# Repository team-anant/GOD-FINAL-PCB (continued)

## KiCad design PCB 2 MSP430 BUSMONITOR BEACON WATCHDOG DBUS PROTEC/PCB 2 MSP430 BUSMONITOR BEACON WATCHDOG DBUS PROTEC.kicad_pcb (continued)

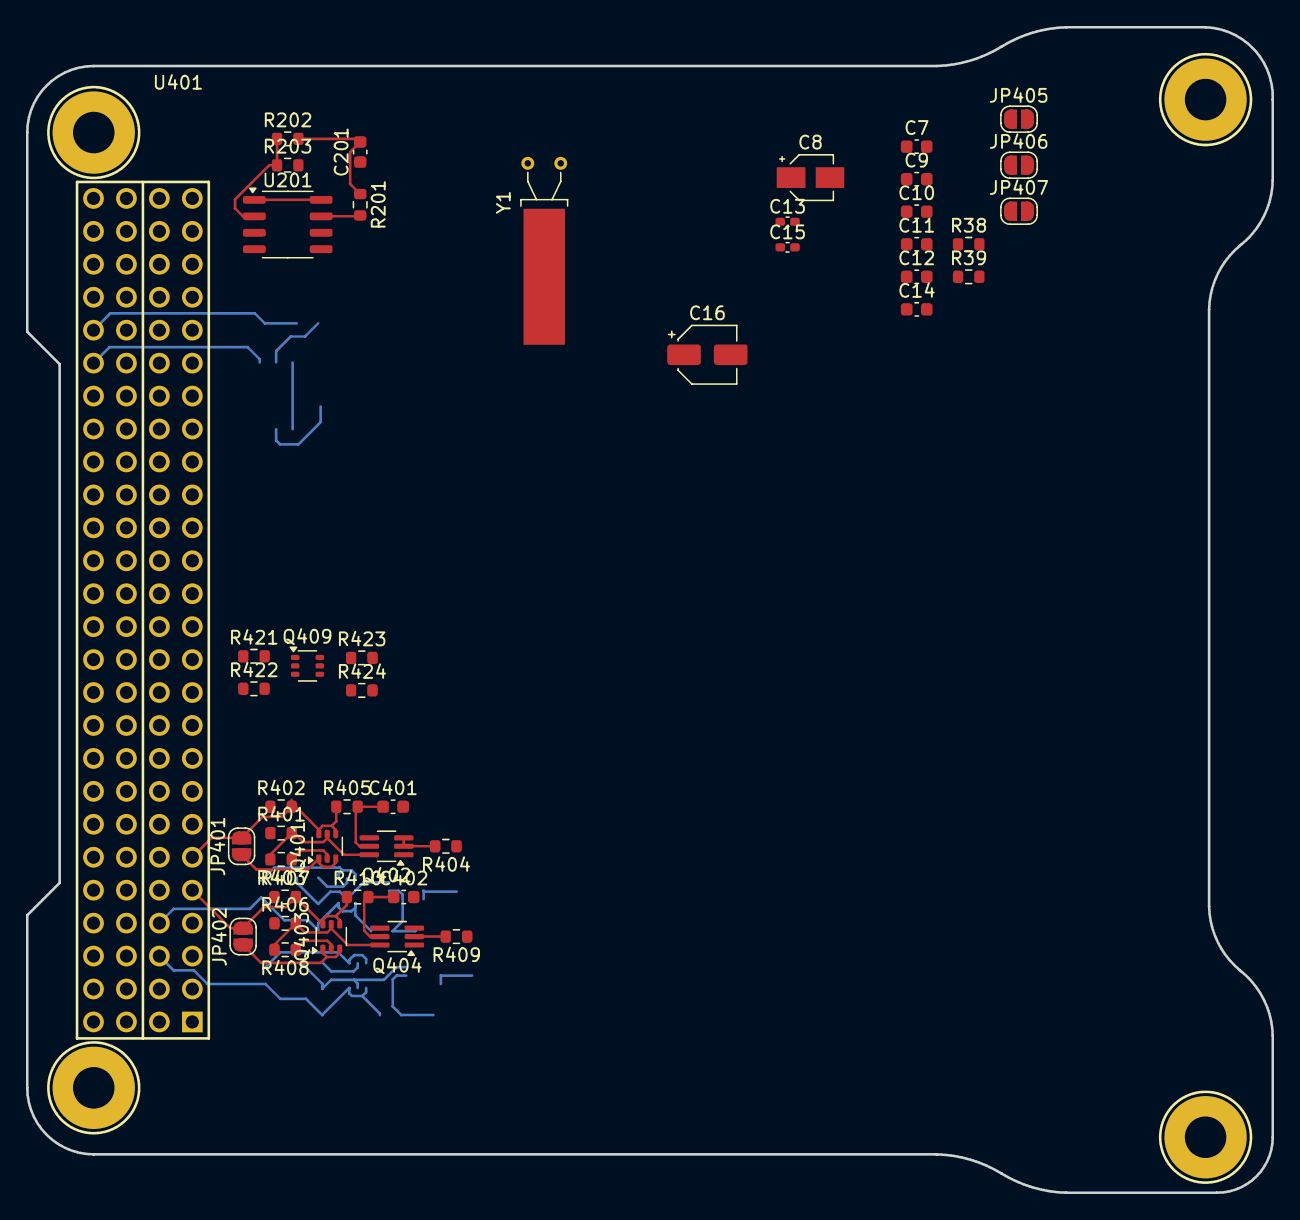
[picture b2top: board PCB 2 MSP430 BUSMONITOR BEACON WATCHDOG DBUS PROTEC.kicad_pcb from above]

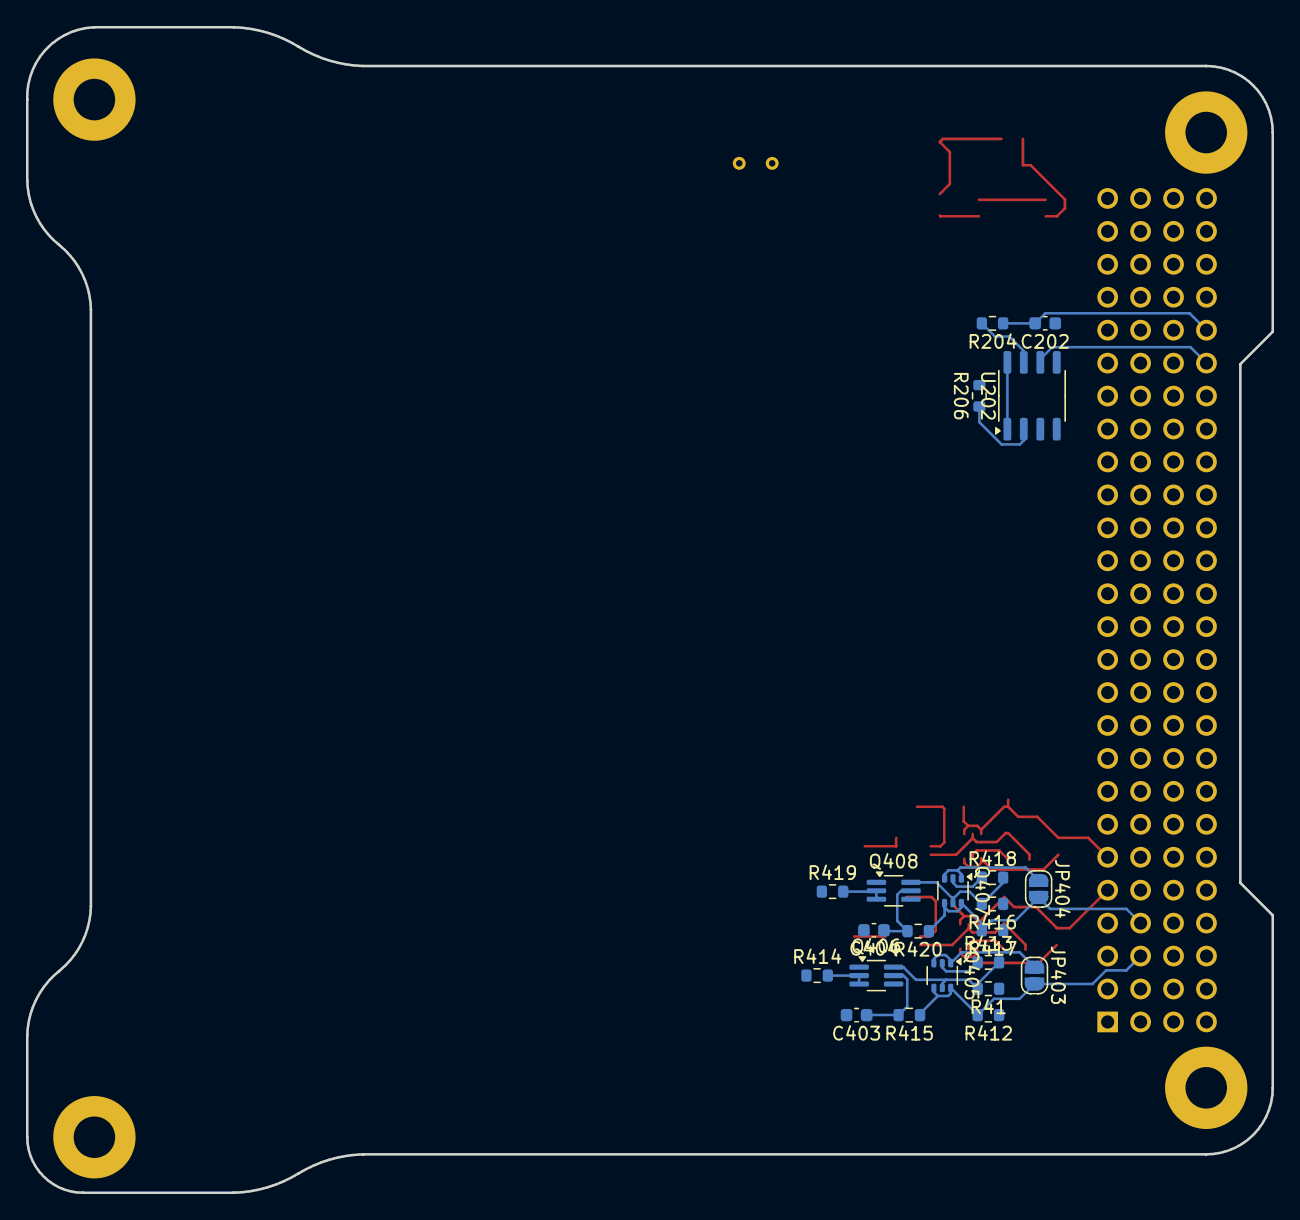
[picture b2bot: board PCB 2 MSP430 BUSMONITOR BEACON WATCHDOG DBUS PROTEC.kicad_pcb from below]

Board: 4 copper layers, 96.0 x 89.9 mm, 67 parts (22 on the bottom side), 40 nets.

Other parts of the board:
R206: 10K; R_0603_1608Metric

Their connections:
3.3V: R206.1; also elsewhere on the board
SWCLK: R206.2; also elsewhere on the board

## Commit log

2024-12-20 ADD 1
2024-12-25 Changes
    Added bucks from old work
    and copied SPV
2024-12-25 New components
2025-01-05 EDITS
2025-01-07 EDITS NTH
2025-01-13 EDITS N+1
2025-01-30 Added some comments in POWERPCB, about bus interface
2025-02-04 Redisgnated components in PCB2 to make more sense
2025-02-13 Change in MSP sch
2025-02-13 Relabeling according to standards
2025-02-14 VCOMMIT
    EDITS N+I
2025-10-17 designblocks
2025-11-01 added components
2025-11-03 one-U pcb start
2025-11-09 primitive one u
2025-11-10 more stuff on one u
